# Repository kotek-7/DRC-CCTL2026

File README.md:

キャチロボ2026用中央制御基板のKiCad回路図データです。

プレビュー (v0.2.1):
https://kicanvas.org/?repo=https%3A%2F%2Fgithub.com%2Fkotek-7%2FDRC-CCTL2026%2Ftree%2Fv0.2.1

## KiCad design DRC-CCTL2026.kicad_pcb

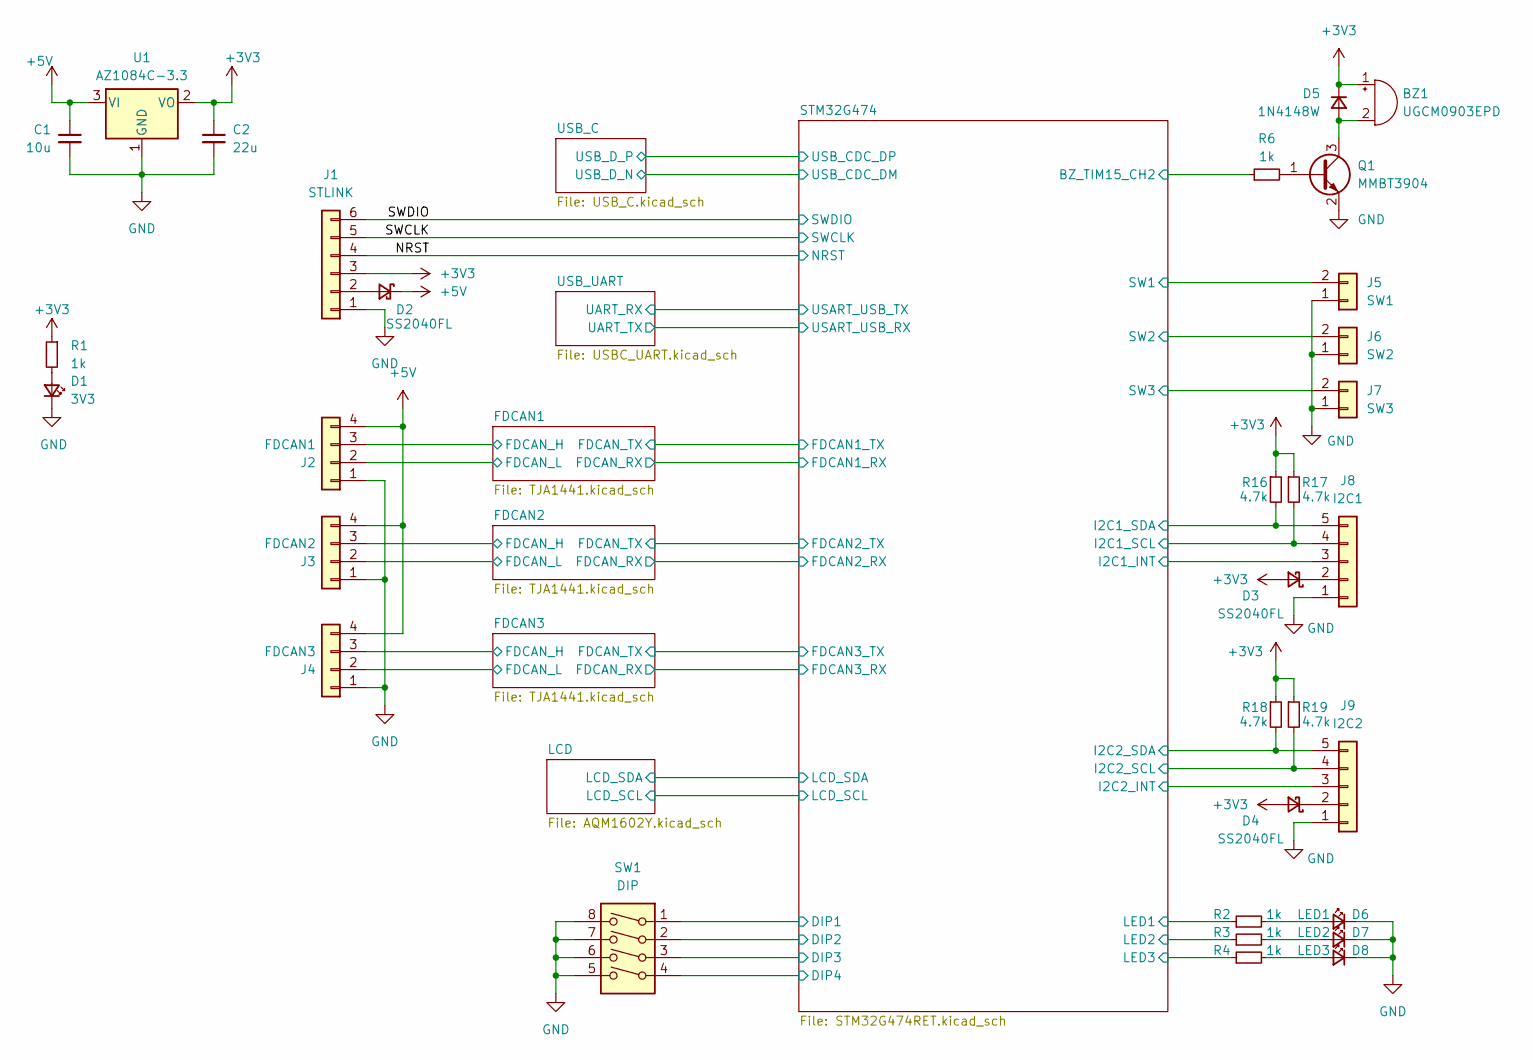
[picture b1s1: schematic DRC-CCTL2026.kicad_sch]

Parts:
BZ1: UGCM0903EPD; UGCM0903EPD_5_0
C1: 10u; C_0805_2012Metric_Pad1.18x1.45mm_HandSolder
C2: 22u; C_0805_2012Metric_Pad1.18x1.45mm_HandSolder
D1: 3V3; LED_0603_1608Metric_Pad1.05x0.95mm_HandSolder
D2, D3, D4: SS2040FL; D_SOD-123F
D5: 1N4148W; D_SOD-123
D6: LED1; LED_0603_1608Metric_Pad1.05x0.95mm_HandSolder
D7: LED2; LED_0603_1608Metric_Pad1.05x0.95mm_HandSolder
D8: LED3; LED_0603_1608Metric_Pad1.05x0.95mm_HandSolder
J1: STLINK; IDC-Header_2x03_P2.54mm_Vertical
J2: FDCAN1; JST_XH_S4B-XH-A_1x04_P2.50mm_Horizontal; LCSC x
J3: FDCAN2; JST_XH_S4B-XH-A_1x04_P2.50mm_Horizontal; LCSC x
J4: FDCAN3; JST_XH_S4B-XH-A_1x04_P2.50mm_Horizontal; LCSC x
J5: SW1; JST_XH_B2B-XH-A_1x02_P2.50mm_Vertical
J6: SW2; JST_XH_B2B-XH-A_1x02_P2.50mm_Vertical
J7: SW3; JST_XH_B2B-XH-A_1x02_P2.50mm_Vertical
J8: I2C1; JST_XH_S5B-XH-A_1x05_P2.50mm_Horizontal
J9: I2C2; JST_XH_S5B-XH-A_1x05_P2.50mm_Horizontal
Q1: MMBT3904; SOT-23
R1, R2, R3, R4, R6: 1k; R_0603_1608Metric_Pad0.98x0.95mm_HandSolder
R16, R17, R18, R19: 4.7k; R_0603_1608Metric_Pad0.98x0.95mm_HandSolder
SW1: DIP; SW_DIP_SPSTx04_Slide_Copal_CHS-04B_W7.62mm_P1.27mm
U1: AZ1084C-3.3; TO-252-2

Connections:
+3V3: BZ1.1 (+), C2.1, D3.2 (A), D4.2 (A), D5.1 (K), J1.3, R1.1, R16.1, R17.1, R18.1, R19.1, U1.2 (VO); also elsewhere on the board
+5V: C1.1, D2.1 (K), J2.4, J3.4, J4.4, U1.3 (VI); also elsewhere on the board
/FDCAN1/FDCAN_H: J2.3; also elsewhere on the board
/FDCAN1/FDCAN_L: J2.2; also elsewhere on the board
/FDCAN2/FDCAN_H: J3.3; also elsewhere on the board
/FDCAN2/FDCAN_L: J3.2; also elsewhere on the board
/FDCAN3/FDCAN_H: J4.3; also elsewhere on the board
/FDCAN3/FDCAN_L: J4.2; also elsewhere on the board
/NRST: J1.4; also elsewhere on the board
/STM32G474/BZ_TIM15_CH2: R6.1; also elsewhere on the board
/STM32G474/DIP1: SW1.1; also elsewhere on the board
/STM32G474/DIP2: SW1.2; also elsewhere on the board
/STM32G474/DIP3: SW1.3; also elsewhere on the board
/STM32G474/DIP4: SW1.4; also elsewhere on the board
/STM32G474/I2C1_INT: J8.3; also elsewhere on the board
/STM32G474/I2C1_SCL: J8.4, R17.2; also elsewhere on the board
/STM32G474/I2C1_SDA: J8.5, R16.2; also elsewhere on the board
/STM32G474/I2C2_INT: J9.3; also elsewhere on the board
/STM32G474/I2C2_SCL: J9.4, R19.2; also elsewhere on the board
/STM32G474/I2C2_SDA: J9.5, R18.2; also elsewhere on the board
/STM32G474/LED1: R2.1; also elsewhere on the board
/STM32G474/LED2: R3.1; also elsewhere on the board
/STM32G474/LED3: R4.1; also elsewhere on the board
/STM32G474/SW1: J5.2; also elsewhere on the board
/STM32G474/SW2: J6.2; also elsewhere on the board
/STM32G474/SW3: J7.2; also elsewhere on the board
/SWCLK: J1.5; also elsewhere on the board
/SWDIO: J1.6; also elsewhere on the board
GND: C1.2, C2.2, D1.1 (K), D6.1 (K), D7.1 (K), D8.1 (K), J1.1, J2.1, J3.1, J4.1, J5.1, J6.1, J7.1, J8.1, J9.1, Q1.2 (E), SW1.5, SW1.6, SW1.7, SW1.8, U1.1 (GND); also elsewhere on the board
unnamed: BZ1.2 (-), D5.2 (A), Q1.3 (C)
unnamed: D1.2 (A), R1.2
unnamed: D2.2 (A), J1.2
unnamed: D3.1 (K), J8.2
unnamed: D4.1 (K), J9.2
unnamed: D6.2 (A), R2.2
unnamed: D7.2 (A), R3.2
unnamed: D8.2 (A), R4.2
unnamed: Q1.1 (B), R6.2

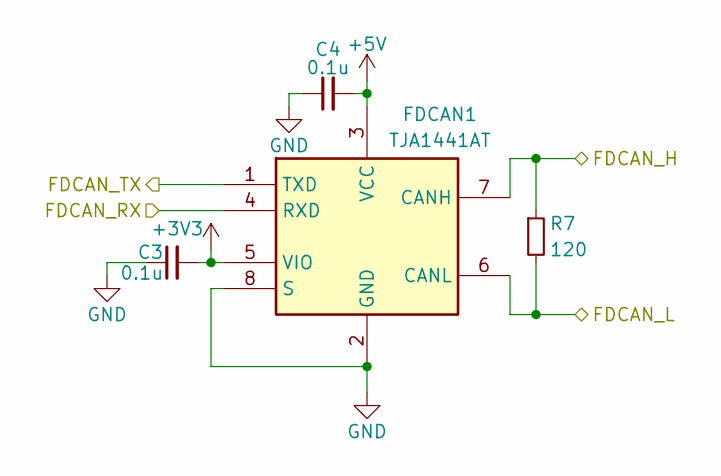
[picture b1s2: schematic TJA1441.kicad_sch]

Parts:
C3, C4: 0.1u; C_0603_1608Metric_Pad1.08x0.95mm_HandSolder
FDCAN1: TJA1441AT; SO8_SOT96-1_NXP; Manufacturer_Part_Number TJA1441AT
R7: 120; R_0603_1608Metric_Pad0.98x0.95mm_HandSolder

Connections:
+3V3: C3.2, FDCAN1.5 (VIO); also elsewhere on the board
+5V: C4.2, FDCAN1.3 (VCC); also elsewhere on the board
/FDCAN1/FDCAN_H: FDCAN1.7 (CANH), R7.1; also elsewhere on the board
/FDCAN1/FDCAN_L: FDCAN1.6 (CANL), R7.2; also elsewhere on the board
/FDCAN1/FDCAN_RX: FDCAN1.4 (RXD); also elsewhere on the board
/FDCAN1/FDCAN_TX: FDCAN1.1 (TXD); also elsewhere on the board
GND: C3.1, C4.1, FDCAN1.2 (GND), FDCAN1.8 (S); also elsewhere on the board

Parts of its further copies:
C5, C6, C7, C8: 0.1u; C_0603_1608Metric_Pad1.08x0.95mm_HandSolder
FDCAN2, FDCAN3: TJA1441AT; SO8_SOT96-1_NXP; Manufacturer_Part_Number TJA1441AT
R8, R9: 120; R_0603_1608Metric_Pad0.98x0.95mm_HandSolder

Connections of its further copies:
+3V3: C5.2, C7.2, FDCAN2.5 (VIO), FDCAN3.5 (VIO); also elsewhere on the board
+5V: C6.2, C8.2, FDCAN2.3 (VCC), FDCAN3.3 (VCC); also elsewhere on the board
/FDCAN2/FDCAN_H: FDCAN2.7 (CANH), R8.1; also elsewhere on the board
/FDCAN2/FDCAN_L: FDCAN2.6 (CANL), R8.2; also elsewhere on the board
/FDCAN2/FDCAN_RX: FDCAN2.4 (RXD); also elsewhere on the board
/FDCAN2/FDCAN_TX: FDCAN2.1 (TXD); also elsewhere on the board
/FDCAN3/FDCAN_H: FDCAN3.7 (CANH), R9.1; also elsewhere on the board
/FDCAN3/FDCAN_L: FDCAN3.6 (CANL), R9.2; also elsewhere on the board
/FDCAN3/FDCAN_RX: FDCAN3.4 (RXD); also elsewhere on the board
/FDCAN3/FDCAN_TX: FDCAN3.1 (TXD); also elsewhere on the board
GND: C5.1, C6.1, C7.1, C8.1, FDCAN2.2 (GND), FDCAN2.8 (S), FDCAN3.2 (GND), FDCAN3.8 (S); also elsewhere on the board

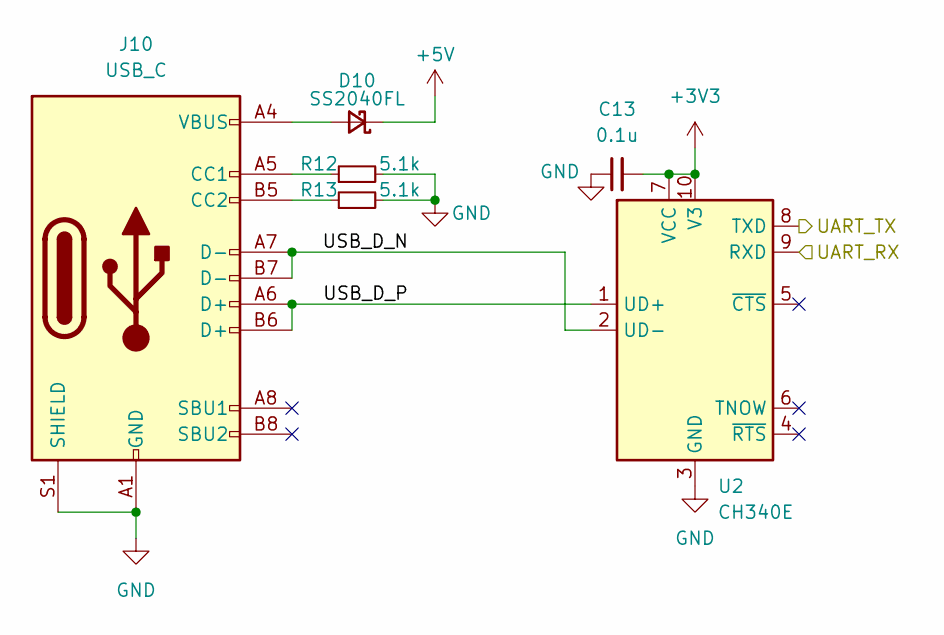
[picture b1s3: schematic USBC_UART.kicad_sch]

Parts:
C13: 0.1u; C_0603_1608Metric_Pad1.08x0.95mm_HandSolder
D10: SS2040FL; D_SOD-123F
J10: USB_C; USB_C_Receptacle_GCT_USB4105-xx-A_16P_TopMnt_Horizontal
R12, R13: 5.1k; R_0603_1608Metric_Pad0.98x0.95mm_HandSolder
U2: CH340E; MSOP-10_3x3mm_P0.5mm

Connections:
+3V3: C13.2, U2.7 (VCC), U2.10 (V3); also elsewhere on the board
+5V: D10.1 (K); also elsewhere on the board
/STM32G474/USART_USB_RX: U2.8 (TXD); also elsewhere on the board
/STM32G474/USART_USB_TX: U2.9 (RXD); also elsewhere on the board
/USB_UART/USB_D_N: J10.A7 (D-), J10.B7 (D-), U2.2 (UD-)
/USB_UART/USB_D_P: J10.A6 (D+), J10.B6 (D+), U2.1 (UD+)
GND: C13.1, J10.A1 (GND), J10.A12 (GND), J10.B1 (GND), J10.B12 (GND), J10.S1 (SHIELD), R12.2, R13.2, U2.3 (GND); also elsewhere on the board
unnamed: D10.2 (A), J10.A4 (VBUS), J10.A9 (VBUS), J10.B4 (VBUS), J10.B9 (VBUS)
unnamed: J10.A5 (CC1), R12.1
unnamed: J10.B5 (CC2), R13.1

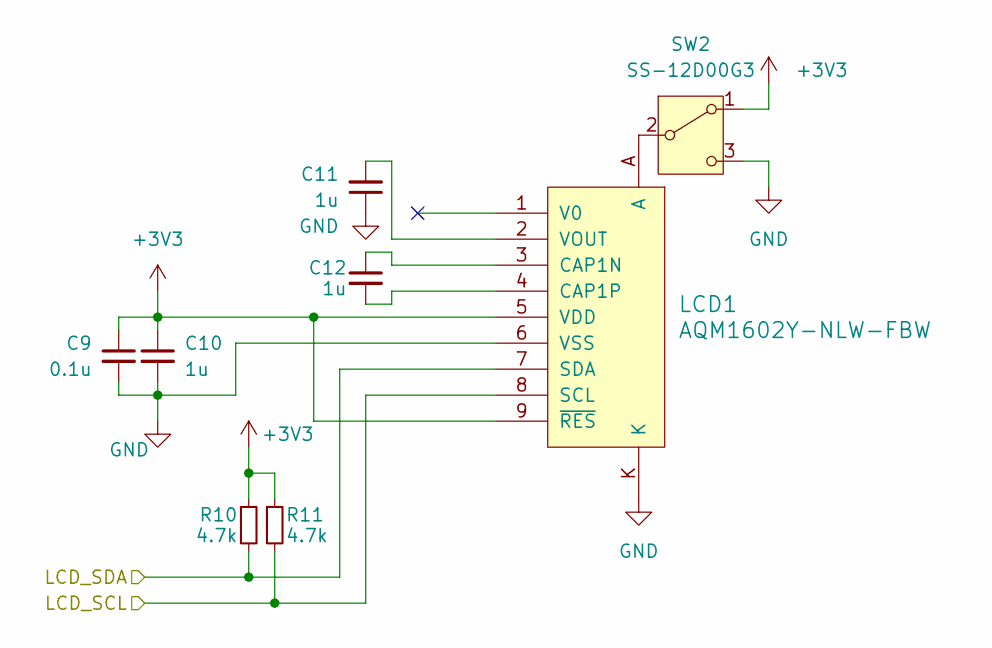
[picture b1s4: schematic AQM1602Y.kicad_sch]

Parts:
C9: 0.1u; C_0603_1608Metric_Pad1.08x0.95mm_HandSolder
C10, C11, C12: 1u; C_0603_1608Metric_Pad1.08x0.95mm_HandSolder
LCD1: AQM1602Y-NLW-FBW; AQM1602Y-NLW
R10, R11: 4.7k; R_0603_1608Metric_Pad0.98x0.95mm_HandSolder
SW2: SS-12D00G3

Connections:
+3V3: C9.1, C10.1, LCD1.5 (VDD), LCD1.9 (~RES), R10.1, R11.1, SW2.1 (A); also elsewhere on the board
/LCD/LCD_SCL: LCD1.8 (SCL), R11.2; also elsewhere on the board
/LCD/LCD_SDA: LCD1.7 (SDA), R10.2; also elsewhere on the board
GND: C9.2, C10.2, C11.1, LCD1.6 (VSS), LCD1.K, SW2.3 (C); also elsewhere on the board
unnamed: C12.1, LCD1.3 (CAP1N)
unnamed: C12.2, LCD1.4 (CAP1P)
unnamed: C11.2, LCD1.2 (VOUT)
unnamed: LCD1.A, SW2.2 (B)

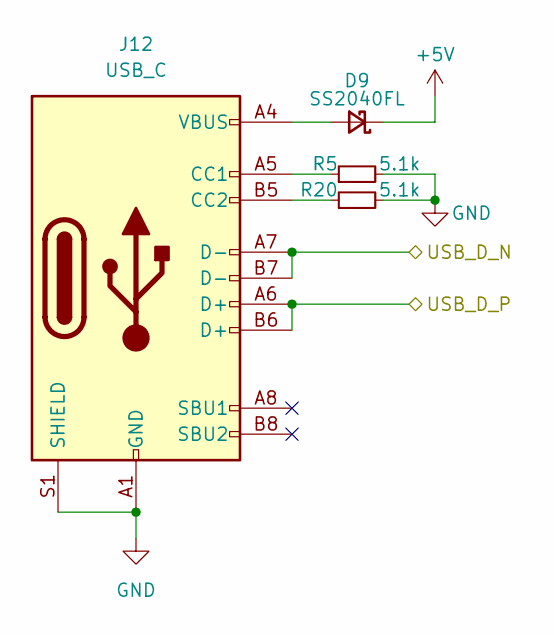
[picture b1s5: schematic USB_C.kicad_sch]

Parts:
D9: SS2040FL; D_SOD-123F
J12: USB_C; USB_C_Receptacle_GCT_USB4105-xx-A_16P_TopMnt_Horizontal
R5, R20: 5.1k; R_0603_1608Metric_Pad0.98x0.95mm_HandSolder

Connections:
+5V: D9.1 (K); also elsewhere on the board
/STM32G474/USB_CDC_DM: J12.A7 (D-), J12.B7 (D-); also elsewhere on the board
/STM32G474/USB_CDC_DP: J12.A6 (D+), J12.B6 (D+); also elsewhere on the board
GND: J12.A1 (GND), J12.A12 (GND), J12.B1 (GND), J12.B12 (GND), J12.S1 (SHIELD), R5.2, R20.2; also elsewhere on the board
unnamed: D9.2 (A), J12.A4 (VBUS), J12.A9 (VBUS), J12.B4 (VBUS), J12.B9 (VBUS)
unnamed: J12.A5 (CC1), R5.1
unnamed: J12.B5 (CC2), R20.1

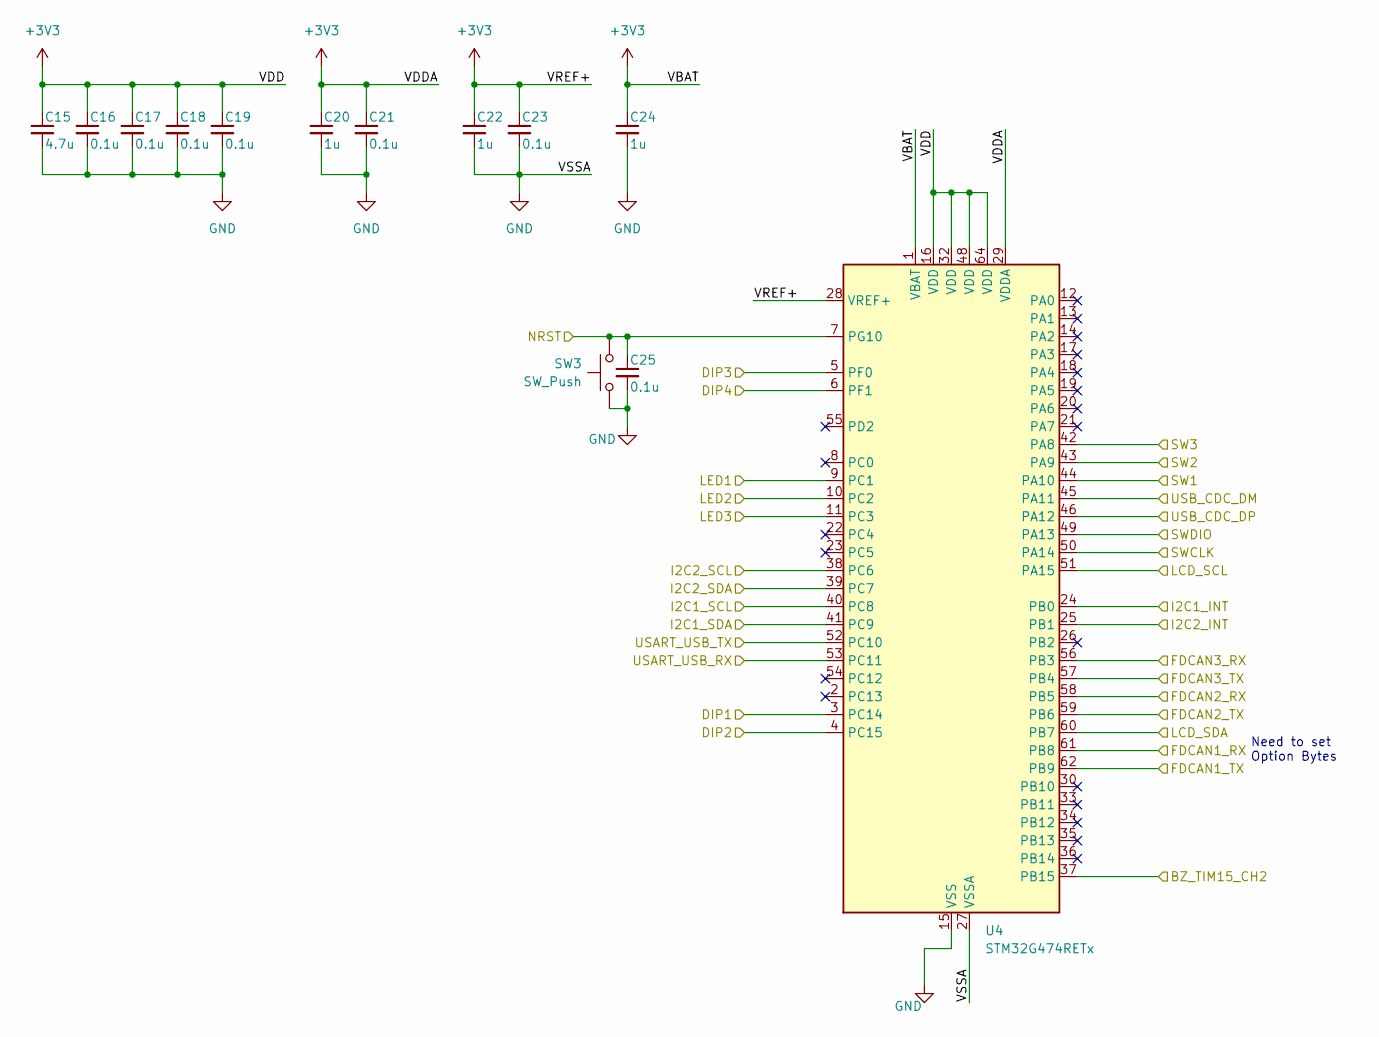
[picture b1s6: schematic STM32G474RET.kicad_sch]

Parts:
C15: 4.7u; C_0805_2012Metric_Pad1.18x1.45mm_HandSolder
C16, C17, C18, C19, C21, C23, C25: 0.1u; C_0603_1608Metric_Pad1.08x0.95mm_HandSolder
C20, C22, C24: 1u; C_0603_1608Metric_Pad1.08x0.95mm_HandSolder
SW3: SW_Push; SW_SPST_EVQPE1
U4: STM32G474RETx; LQFP-64_10x10mm_P0.5mm

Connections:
+3V3: C15.1, C16.1, C17.1, C18.1, C19.1, C20.1, C21.1, C22.1, C23.1, C24.1, U4.1 (VBAT), U4.16 (VDD), U4.28 (VREF+), U4.29 (VDDA), U4.32 (VDD), U4.48 (VDD), U4.64 (VDD); also elsewhere on the board
/FDCAN1/FDCAN_RX: U4.61 (PB8); also elsewhere on the board
/FDCAN1/FDCAN_TX: U4.62 (PB9); also elsewhere on the board
/FDCAN2/FDCAN_RX: U4.58 (PB5); also elsewhere on the board
/FDCAN2/FDCAN_TX: U4.59 (PB6); also elsewhere on the board
/FDCAN3/FDCAN_RX: U4.56 (PB3); also elsewhere on the board
/FDCAN3/FDCAN_TX: U4.57 (PB4); also elsewhere on the board
/LCD/LCD_SCL: U4.51 (PA15); also elsewhere on the board
/LCD/LCD_SDA: U4.60 (PB7); also elsewhere on the board
/NRST: C25.1, SW3.1, U4.7 (PG10); also elsewhere on the board
/STM32G474/BZ_TIM15_CH2: U4.37 (PB15); also elsewhere on the board
/STM32G474/DIP1: U4.3 (PC14); also elsewhere on the board
/STM32G474/DIP2: U4.4 (PC15); also elsewhere on the board
/STM32G474/DIP3: U4.5 (PF0); also elsewhere on the board
/STM32G474/DIP4: U4.6 (PF1); also elsewhere on the board
/STM32G474/I2C1_INT: U4.24 (PB0); also elsewhere on the board
/STM32G474/I2C1_SCL: U4.40 (PC8); also elsewhere on the board
/STM32G474/I2C1_SDA: U4.41 (PC9); also elsewhere on the board
/STM32G474/I2C2_INT: U4.25 (PB1); also elsewhere on the board
/STM32G474/I2C2_SCL: U4.38 (PC6); also elsewhere on the board
/STM32G474/I2C2_SDA: U4.39 (PC7); also elsewhere on the board
/STM32G474/LED1: U4.9 (PC1); also elsewhere on the board
/STM32G474/LED2: U4.10 (PC2); also elsewhere on the board
/STM32G474/LED3: U4.11 (PC3); also elsewhere on the board
/STM32G474/SW1: U4.44 (PA10); also elsewhere on the board
/STM32G474/SW2: U4.43 (PA9); also elsewhere on the board
/STM32G474/SW3: U4.42 (PA8); also elsewhere on the board
/STM32G474/USART_USB_RX: U4.53 (PC11); also elsewhere on the board
/STM32G474/USART_USB_TX: U4.52 (PC10); also elsewhere on the board
/STM32G474/USB_CDC_DM: U4.45 (PA11); also elsewhere on the board
/STM32G474/USB_CDC_DP: U4.46 (PA12); also elsewhere on the board
/SWCLK: U4.50 (PA14); also elsewhere on the board
/SWDIO: U4.49 (PA13); also elsewhere on the board
GND: C15.2, C16.2, C17.2, C18.2, C19.2, C20.2, C21.2, C22.2, C23.2, C24.2, C25.2, SW3.2, U4.15 (VSS), U4.27 (VSSA), U4.31 (VSS), U4.47 (VSS), U4.63 (VSS); also elsewhere on the board

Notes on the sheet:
Need to set Option Bytes

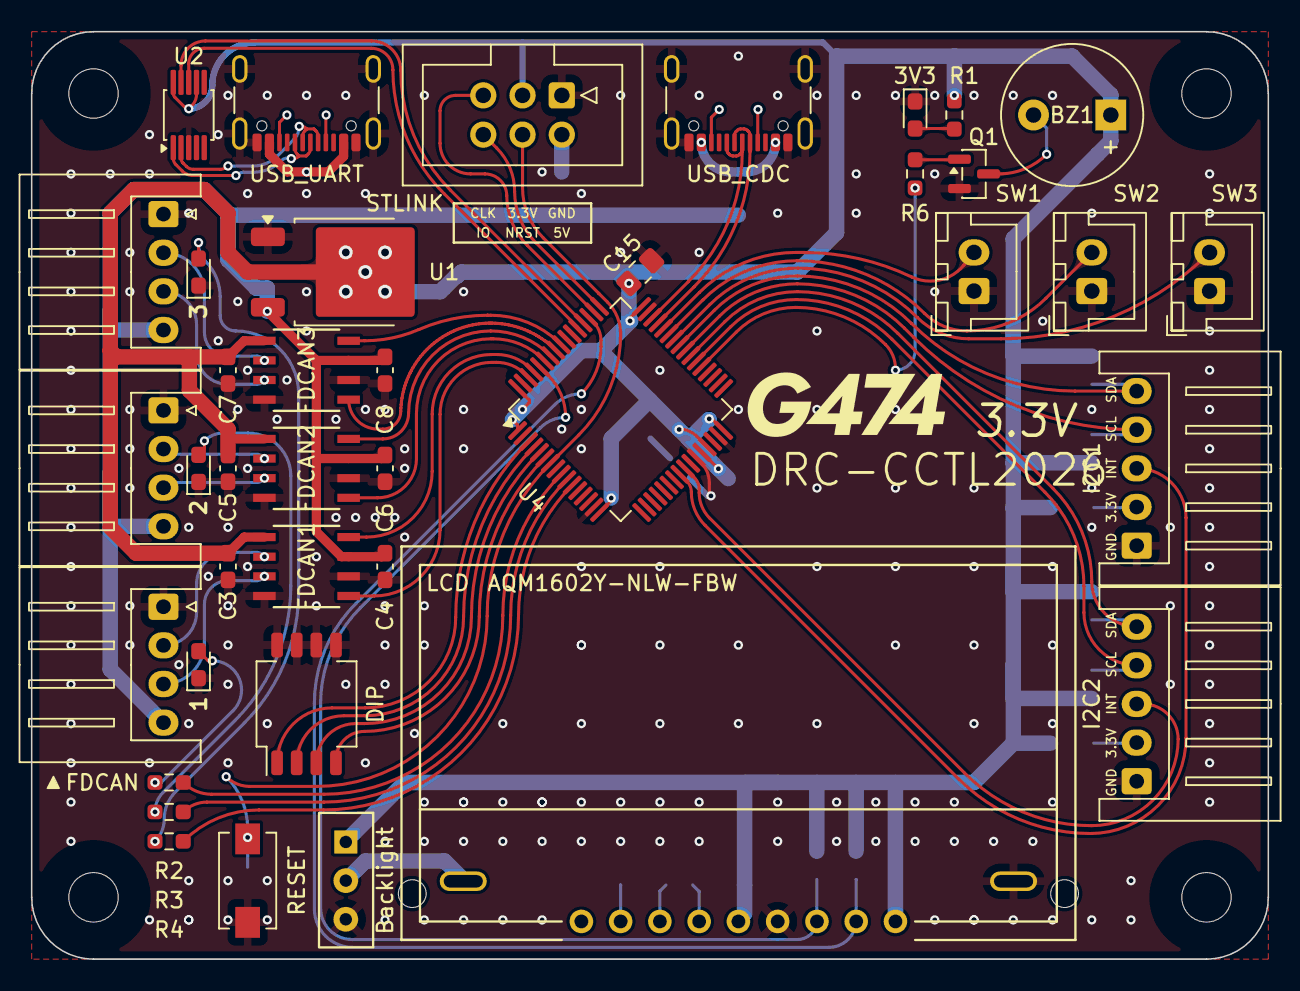
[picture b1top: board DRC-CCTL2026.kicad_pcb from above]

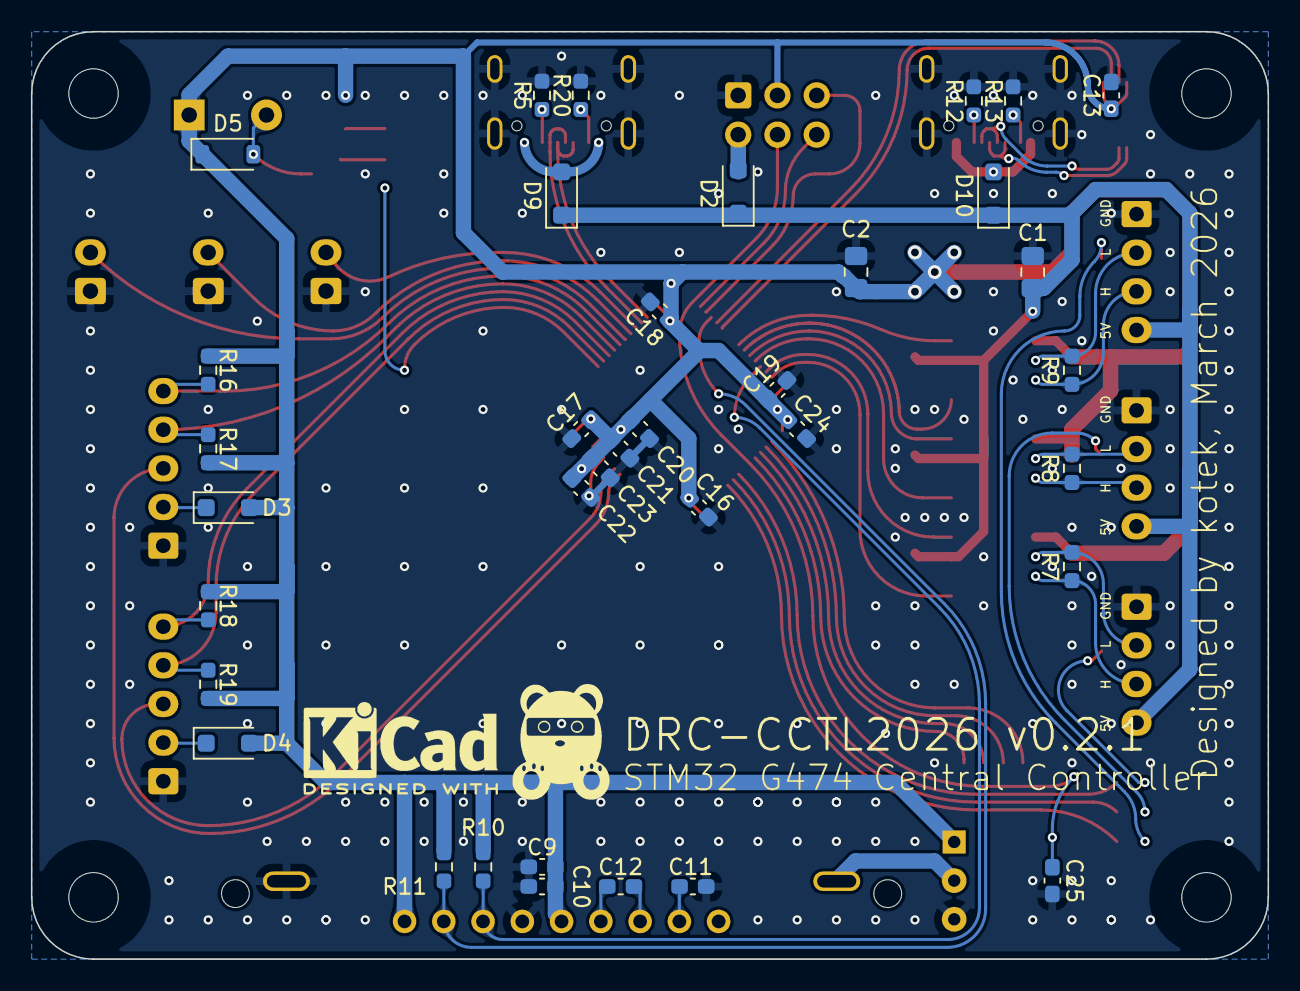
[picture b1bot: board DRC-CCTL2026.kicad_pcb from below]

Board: 2 copper layers, 80.0 x 60.0 mm, 75 parts (36 on the bottom side), 62 nets.

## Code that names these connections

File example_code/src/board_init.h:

#pragma once

#include <Arduino.h>

constexpr uint8_t LED_BI = PA5;
constexpr uint8_t RGB_DATA = PA6;
constexpr uint8_t I2C_INT = PA10;
constexpr uint8_t BUZZER = PA15;

constexpr uint8_t DIP4 = PB12;
constexpr uint8_t DIP3 = PB13;
constexpr uint8_t DIP2 = PB14;
constexpr uint8_t DIP1 = PB15;

constexpr uint8_t SW3 = PC13;
constexpr uint8_t SW2 = PC14;
constexpr uint8_t SW1 = PC15;

constexpr uint8_t FDCAN3_RX = PB3;
constexpr uint8_t FDCAN3_TX = PB4;
constexpr uint8_t FDCAN2_RX = PB5;
constexpr uint8_t FDCAN2_TX = PB6;
constexpr uint8_t FDCAN1_RX = PB8;
constexpr uint8_t FDCAN1_TX = PB9;

constexpr uint8_t USART_TX = PC10;
constexpr uint8_t USART_RX = PC11;

constexpr uint8_t I2C_EXT_SDA = PA8;
constexpr uint8_t I2C_EXT_SCL = PA9;
constexpr uint8_t LCD_SCL = PC8;
constexpr uint8_t LCD_SDA = PC9;

constexpr uint8_t USB_DM_PIN = PA11;
constexpr uint8_t USB_DP_PIN = PA12;

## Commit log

2026-03-31 シルクスクリーン被りを修正
2026-03-31 LCDの3dモデルを追加、スルーホールを調整
2026-03-31 DRCを実行
2026-03-31 画像を差し替え
2026-03-31 T字配線にフィレットを追加
2026-03-31 不要なビアを削除
2026-03-31 配線を改善
2026-03-31 ledの抵抗値を変更
2026-04-01 バージョンを変更
2026-04-02 パターン引き直し・部品配置変更
2026-04-02 drc実行
2026-04-03 v10対応
2026-04-04 gitignore を変更
2026-04-04 Revert "v10対応"
    This reverts commit baf912c2f8df2bec777aa3791820c88b0f144cdf.
2026-04-04 CANの終端抵抗を削除、シルクスクリーンを調整
2026-04-05 JLCPCB用に書き出し、v0.1.0
2026-04-12 サンプルコードを追加
2026-04-14 platformio.iniのenvを統合
2026-04-14 ファイルを移動
2026-04-14 STM32 VSCode Extention に対応
2026-04-14 halで各サンプルを記述
2026-04-15 pio の不要な例は削除
2026-04-17 v0.2.0
2026-04-17 v0.2.1, USB CDC に対応
2026-04-17 JLCPCB用に書き出し
2026-04-17 JLCPCB用に書き出し2
2026-04-17 バージョン表記を修正・JLCPCBに書き出し
2026-05-02 bom を生成
2026-05-12 サンプルをv0.2.1に向けて追加
